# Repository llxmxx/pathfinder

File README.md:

# pathfinder
custom pcb controller board and e-fidget. pressing certain buttons(at certain times) lights up certain leds. if you hold down button3, the buttons can be used to change brightness and nagivate around the board.

### pcb:

### schematic:

### BoM:
| Name | Purpose | Quantity | Total Cost (USD) | Link	| Distributor	|
|------|---------|----------|------------------|------|-------------|
| cherry mx2a switches | buttons for input | 10 | 4.51 | https://meckeys.com/shop/accessories/keyboard-accessories/key-switches/cherry-mx2a-switch/?attribute_pa_cherry-mx=blue-rgb | Meckeys	|
| led | to light up! | 10	| 0.13 | https://robocraze.com/products/5mm-white-blue-led-pack-of-10?variant=40192389120153 | Robocraze |
| keycaps | to cover the switches | 5 | 1.04 | https://meckeys.com/shop/accessories/keyboard-accessories/keycaps/blank/blank-dsa-keycaps-1u/?attribute_pa_variations=off-white | Meckeys |
| xiao rp2040 | where the inputs from buttons go and where the outputs for leds come from | 1 | 6.42 | https://robocraze.com/products/seeed-studio-xiao-rp2040-development-board?variant=47742255562976 | Robocraze |
| pcb |	printed circuit board to assemble and connect components | 5 | 4 | https://jlcpcb.com/ | JLCPCB |

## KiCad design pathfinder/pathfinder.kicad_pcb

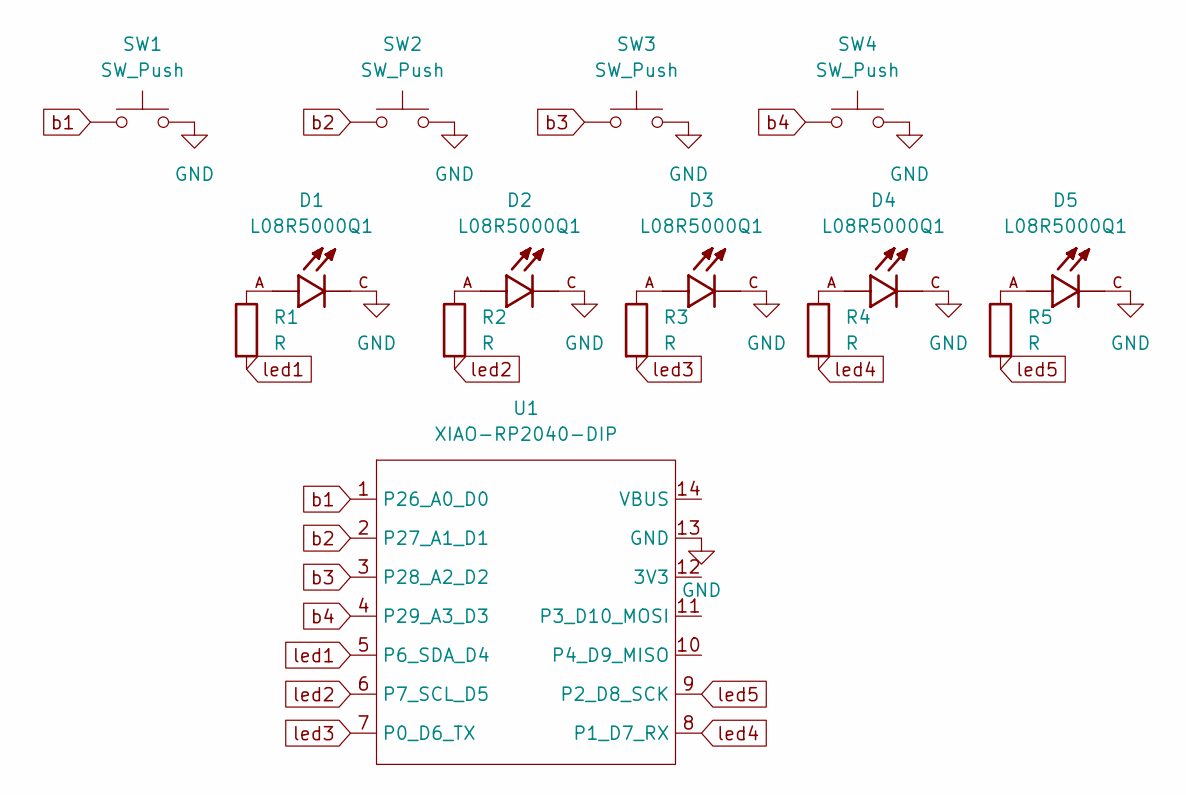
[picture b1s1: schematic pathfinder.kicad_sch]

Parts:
D1, D2, D3, D4, D5: L08R5000Q1; LEDRD254W57D500H1070; PARTREV NA
R1, R2, R3, R4, R5: R; R_Axial_DIN0204_L3.6mm_D1.6mm_P5.08mm_Horizontal
SW1, SW2, SW3, SW4: SW_Push; SW_Cherry_MX_1.00u_PCB
U1: XIAO-RP2040-DIP

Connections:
GND: D1.C, D2.C, D3.C, D4.C, D5.C, SW1.2, SW2.2, SW3.2, SW4.2, U1.13 (GND)
unnamed: D1.A, R1.1
unnamed: D2.A, R2.1
unnamed: D3.A, R3.1
unnamed: D4.A, R4.1
unnamed: D5.A, R5.1
b1: SW1.1, U1.1 (P26_A0_D0)
b2: SW2.1, U1.2 (P27_A1_D1)
b3: SW3.1, U1.3 (P28_A2_D2)
b4: SW4.1, U1.4 (P29_A3_D3)
led1: R1.2, U1.5 (P6_SDA_D4)
led2: R2.2, U1.6 (P7_SCL_D5)
led3: R3.2, U1.7 (P0_D6_TX)
led4: R4.2, U1.8 (P1_D7_RX)
led5: R5.2, U1.9 (P2_D8_SCK)

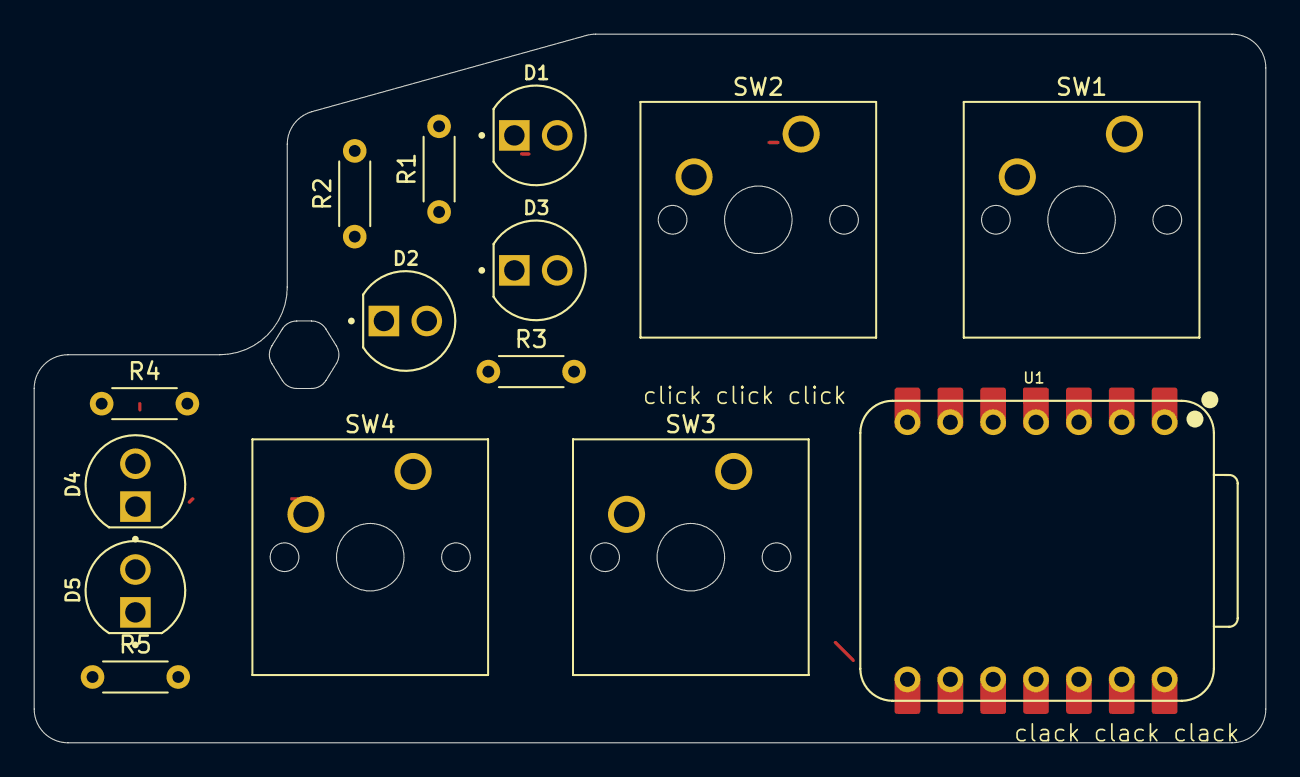
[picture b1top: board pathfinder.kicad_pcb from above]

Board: 2 copper layers, 73.0 x 42.0 mm, 15 parts (0 on the bottom side), 15 nets.

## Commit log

2026-05-17 made the schematic and designed the pcb
2026-05-21 untested firmware
    it'll probably works
2026-05-21 added silkscreen
2026-05-21 gerber and drill files
2026-06-01 routing
